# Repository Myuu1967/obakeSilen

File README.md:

# obakeSilen                ※この回路図はKiCAD7を使用して書いたものです。お気を付けください。<br>
- FPGA/TB4004/src                間違えてpushしてしまったフォルダーです。気にしないでください<br>
- footprint/Library.pretty       KiCADのプリント基板の図面用のライブラリです。ご自身のKiCADに登録すると私のフットプリントが描画されます（お手数おかけします）<br>
- symnbol                        KiCADの回路図で使用されているシンボルのライブラリです。登録することで私が製作したシンボルが使用できます（上に同じ）<br>
- .gitignore                    .gitignoreです。<br>
- NE555.csv                     この回路に必要な部品の部品表です。<br>
- NE555.kicad_*(4個あります)    　KiCAD用のファイルです（KiCAD7用です。新しいバージョンでも保存したりしなければ閲覧はできます）<br>
- NE555.pdf                      この回路の回路図です（pdfファイルです）<br>
- README.md                      このファイルです<br>

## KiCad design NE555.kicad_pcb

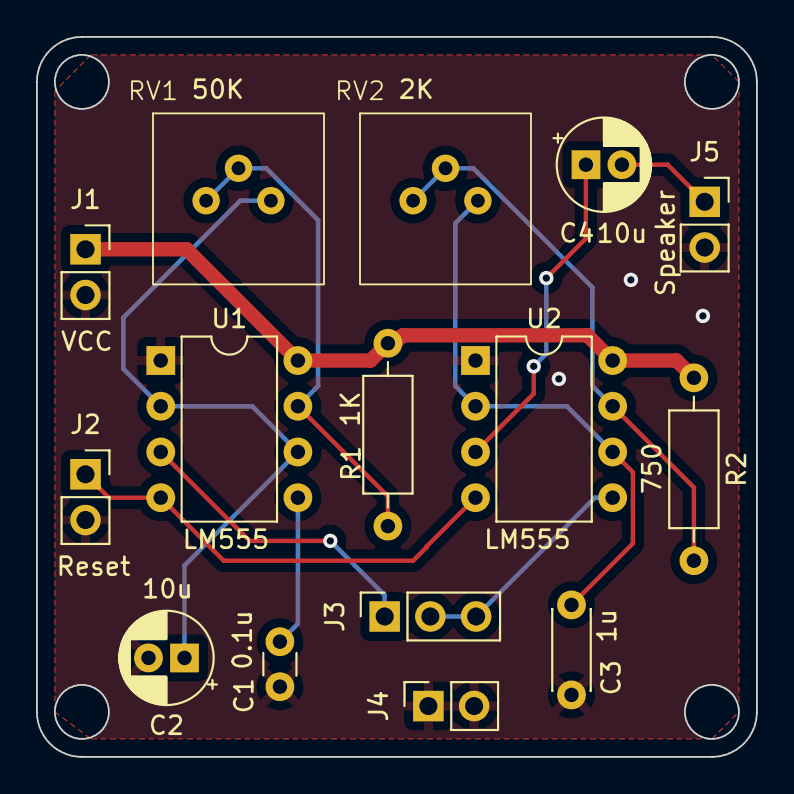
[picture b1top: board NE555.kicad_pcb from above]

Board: 2 copper layers, 40.0 x 40.0 mm, 15 parts (0 on the bottom side), 12 nets.

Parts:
C1: 0.1u; C_Disc_D3.0mm_W1.6mm_P2.50mm
C2, C4: 10u; CP_Radial_D5.0mm_P2.00mm
C3: 1u; C_Disc_D4.3mm_W1.9mm_P5.00mm
J1, J2, J4, J5: Conn_01x02_Socket; PinSocket_1x02_P2.54mm_Vertical
J3: Conn_01x03_Socket; PinSocket_1x03_P2.54mm_Vertical
R1: 1K; R_Axial_DIN0207_L6.3mm_D2.5mm_P10.16mm_Horizontal
R2: 750; R_Axial_DIN0207_L6.3mm_D2.5mm_P10.16mm_Horizontal
RV1: 50K; 50K_VR
RV2: 2K; 50K_VR
U1, U2: LM555xN; DIP-8_W7.62mm

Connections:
+8V: J1.1, R1.1, R2.1, U1.8 (VCC), U2.8 (VCC)
GND: C1.2, C2.2, C3.2, J1.2, J2.2, J4.1, J4.2, J5.2, U1.1 (GND), U2.1 (GND)
unnamed: J2.1, U1.4 (R), U2.4 (R)
unnamed: J3.1, U1.3 (Q)
unnamed: J3.2, J3.3, U2.5 (CV)
unnamed: C4.2, J5.1
unnamed: C1.1, U1.5 (CV)
unnamed: R1.2, RV1.1, RV1.2, U1.7 (DIS)
unnamed: C2.1, RV1.3, U1.2 (TR), U1.6 (THR)
unnamed: R2.2, RV2.1, RV2.2, U2.7 (DIS)
unnamed: C4.1, U2.3 (Q)
unnamed: C3.1, RV2.3, U2.2 (TR), U2.6 (THR)

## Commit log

2025-07-21 Update README.md
    内容を書き換えました
2025-07-21 Update README.md
    書き換えました
2025-07-26 pull from GitHub. Add new files
2025-07-28 pc,stack,命令のフェッチの部分に取り組んだ
2025-07-29 minor change
2025-07-29 Add .gitignore to exclude unnecessary files
2025-07-31 Update README.md
    内容をバージョンアップしました。
    ご活用ください
2025-07-31 Update README.md
    <br>を挿入しました
2025-07-31 Update README.md
    '-'とスペース2個を行頭と項目の次のとこに挿入しました
2025-07-31 Update README.md
    スペース4つを挿入した
